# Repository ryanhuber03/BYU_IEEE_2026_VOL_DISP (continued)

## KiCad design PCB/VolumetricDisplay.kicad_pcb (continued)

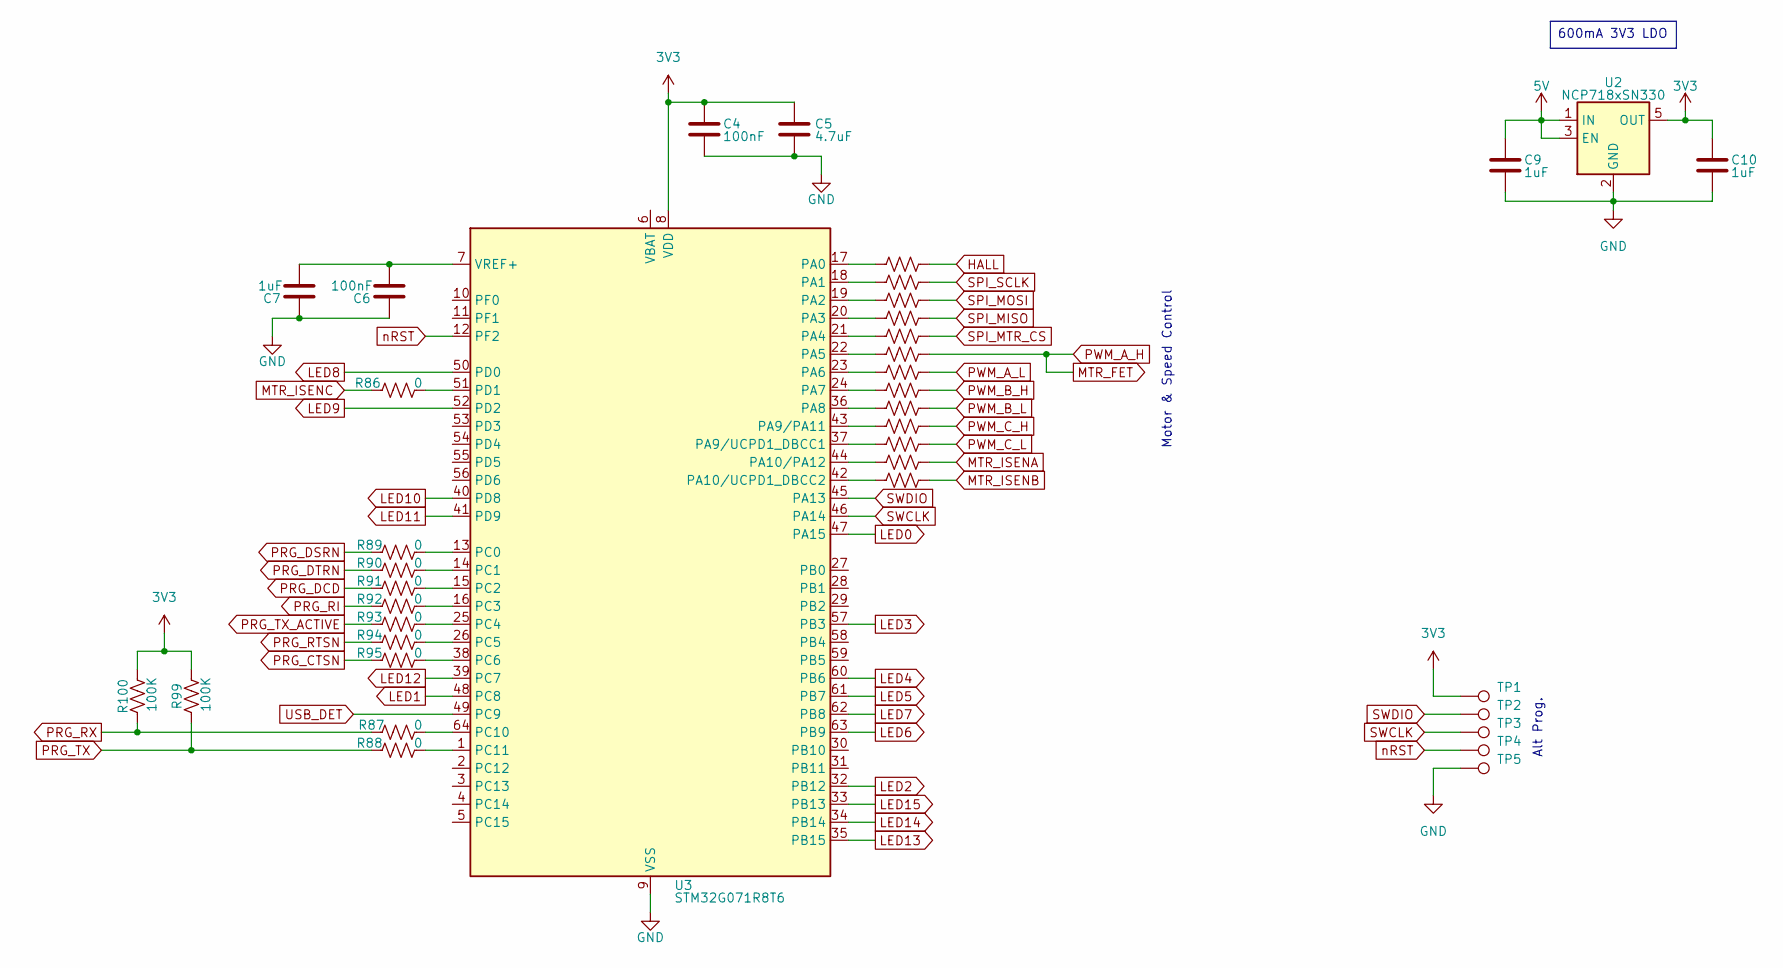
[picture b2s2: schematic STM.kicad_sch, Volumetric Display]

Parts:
C4, C6: 100nF; C_0402_1005Metric_Pad0.74x0.62mm_HandSolder
C5: 4.7uF; C_0402_1005Metric_Pad0.74x0.62mm_HandSolder
C7, C9, C10: 1uF; C_0603_1608Metric_Pad1.08x0.95mm_HandSolder
R74, R75, R76, R77, R78, R79, R80, R81, R82, R83, R84, R85, R86, R87, R88, R89, R90, R91, R92, R93, R94, R95, R96: 0; R_0603_1608Metric_Pad0.98x0.95mm_HandSolder
R99, R100: 100K; R_0603_1608Metric_Pad0.98x0.95mm_HandSolder
TP1, TP2, TP3, TP4, TP5: TestPoint; TestPoint_Pad_D1.5mm
U2: NCP718xSN330; SOT-23-5
U3: STM32G071R8T6; LQFP-64_10x10mm_P0.5mm

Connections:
3V3: C4.1, C5.1, C10.1, R99.1, R100.2, TP1.1 (1_1), U2.5 (OUT), U3.8 (VDD); also elsewhere on the board
5V: C9.1, U2.1 (IN), U2.3 (EN); also elsewhere on the board
GND: C4.2, C5.2, C6.1, C7.1, C9.2, C10.2, TP5.1 (1_1), U2.2 (GND), U3.9 (VSS); also elsewhere on the board
HALL: R96.2; also elsewhere on the board
LED0: U3.47 (PA15); also elsewhere on the board
LED1: U3.48 (PC8); also elsewhere on the board
LED2: U3.32 (PB12); also elsewhere on the board
LED3: U3.57 (PB3); also elsewhere on the board
LED4: U3.60 (PB6); also elsewhere on the board
LED5: U3.61 (PB7); also elsewhere on the board
LED6: U3.63 (PB9); also elsewhere on the board
LED7: U3.62 (PB8); also elsewhere on the board
LED8: U3.50 (PD0); also elsewhere on the board
LED9: U3.52 (PD2); also elsewhere on the board
LED10: U3.40 (PD8); also elsewhere on the board
LED11: U3.41 (PD9); also elsewhere on the board
LED12: U3.39 (PC7); also elsewhere on the board
LED13: U3.35 (PB15); also elsewhere on the board
LED14: U3.34 (PB14); also elsewhere on the board
LED15: U3.33 (PB13); also elsewhere on the board
MTR_FET: R78.2; also elsewhere on the board
MTR_ISENA: R84.2; also elsewhere on the board
MTR_ISENB: R85.2; also elsewhere on the board
MTR_ISENC: R86.2; also elsewhere on the board
unnamed: R96.1, U3.17 (PA0)
unnamed: R74.1, U3.18 (PA1)
unnamed: R75.1, U3.19 (PA2)
unnamed: R76.1, U3.20 (PA3)
unnamed: R77.1, U3.21 (PA4)
unnamed: R78.1, U3.22 (PA5)
unnamed: R79.1, U3.23 (PA6)
unnamed: R80.1, U3.24 (PA7)
unnamed: R81.1, U3.36 (PA8)
unnamed: R82.1, U3.43 (PA9/PA11)
unnamed: R83.1, U3.37 (PA9/UCPD1_DBCC1)
unnamed: R84.1, U3.44 (PA10/PA12)
unnamed: R85.1, U3.42 (PA10/UCPD1_DBCC2)
unnamed: R89.2, U3.13 (PC0)
unnamed: R90.2, U3.14 (PC1)
unnamed: R91.2, U3.15 (PC2)
unnamed: R92.2, U3.16 (PC3)
unnamed: R93.2, U3.25 (PC4)
unnamed: R94.2, U3.26 (PC5)
unnamed: R95.2, U3.38 (PC6)
unnamed: R87.2, U3.64 (PC10)
unnamed: R88.2, U3.1 (PC11)
unnamed: R86.1, U3.51 (PD1)
unnamed: C6.2, C7.2, U3.7 (VREF+)
PRG_CTSN: R95.1; also elsewhere on the board
PRG_DCD: R91.1; also elsewhere on the board
PRG_DSRN: R89.1; also elsewhere on the board
PRG_DTRN: R90.1; also elsewhere on the board
PRG_RI: R92.1; also elsewhere on the board
PRG_RTSN: R94.1; also elsewhere on the board
PRG_RX: R87.1, R100.1; also elsewhere on the board
PRG_TX: R88.1, R99.2; also elsewhere on the board
PRG_TX_ACTIVE: R93.1; also elsewhere on the board
PWM_A_L: R79.2; also elsewhere on the board
PWM_B_H: R80.2; also elsewhere on the board
PWM_B_L: R81.2; also elsewhere on the board
PWM_C_H: R82.2; also elsewhere on the board
PWM_C_L: R83.2; also elsewhere on the board
SPI_MISO: R76.2; also elsewhere on the board
SPI_MOSI: R75.2; also elsewhere on the board
SPI_MTR_CS: R77.2; also elsewhere on the board
SPI_SCLK: R74.2; also elsewhere on the board
SWCLK: TP3.1 (1_1), U3.46 (PA14)
SWDIO: TP2.1 (1_1), U3.45 (PA13)
USB_DET: U3.49 (PC9); also elsewhere on the board
nRST: TP4.1 (1_1), U3.12 (PF2)

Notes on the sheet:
Motor & Speed Control
Alt Prog.
600mA 3V3 LDO

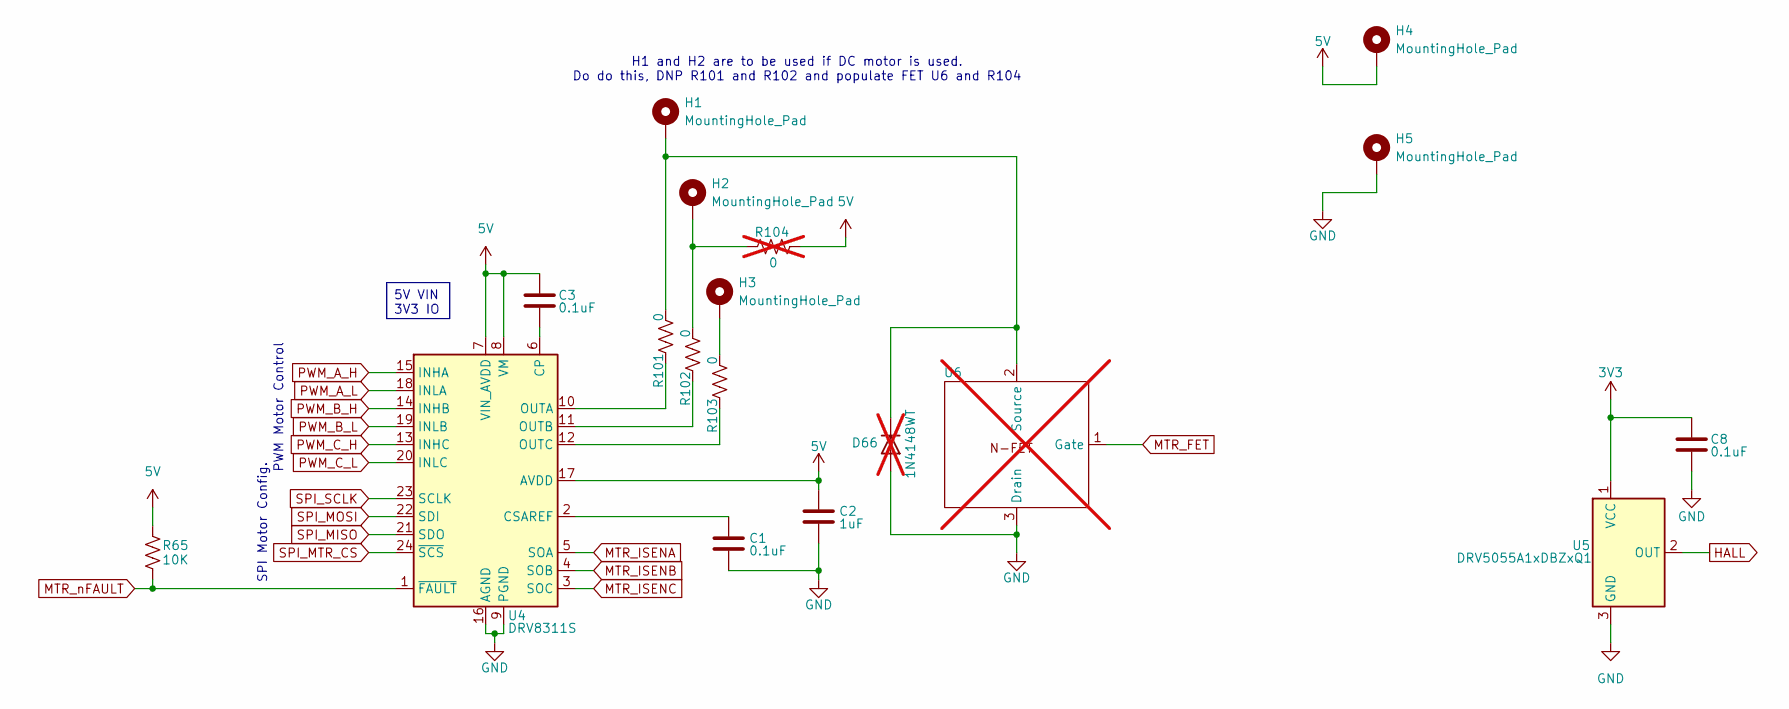
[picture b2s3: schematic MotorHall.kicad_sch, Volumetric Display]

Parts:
C1, C3: 0.1uF; C_0402_1005Metric_Pad0.74x0.62mm_HandSolder
C2: 1uF; C_0402_1005Metric_Pad0.74x0.62mm_HandSolder
C8: 0.1uF; C_0603_1608Metric_Pad1.08x0.95mm_HandSolder
D66: 1N4148WT; D_SOD-323_HandSoldering; not fitted
H1, H2, H3, H4, H5: MountingHole_Pad; 28AWG Pad
R65: 10K; R_0603_1608Metric_Pad0.98x0.95mm_HandSolder
R101, R102, R103: 0; R_0603_1608Metric_Pad0.98x0.95mm_HandSolder
R104: 0; R_0603_1608Metric_Pad0.98x0.95mm_HandSolder; not fitted
U4: DRV8311S; Texas_RRW0024A_WQFN-24-1EP_3x3mm_P0.4mm_EP1.9x1.9mm
U5: DRV5055A1xDBZxQ1; SOT-23
U6: SOT-23_Handsoldering; not fitted

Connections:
3V3: C8.2, U5.1 (VCC); also elsewhere on the board
5V: C2.1, C3.2, H4.1 (1_1), R65.1, R104.1, U4.7 (VIN_AVDD), U4.8 (VM), U4.17 (AVDD); also elsewhere on the board
GND: C1.1, C2.2, C8.1, D66.2 (A), H5.1 (1_1), U4.9 (PGND), U4.16 (AGND), U4.25 (PGND), U5.3 (GND), U6.3 (Drain); also elsewhere on the board
HALL: U5.2 (OUT); also elsewhere on the board
MTR_FET: U4.15 (INHA), U6.1 (Gate); also elsewhere on the board
MTR_ISENA: U4.5 (SOA); also elsewhere on the board
MTR_ISENB: U4.4 (SOB); also elsewhere on the board
MTR_ISENC: U4.3 (SOC); also elsewhere on the board
MTR_nFAULT: R65.2, U4.1 (~FAULT)
unnamed: D66.1 (K), H1.1 (1_1), R101.1, U6.2 (Source)
unnamed: H2.1 (1_1), R102.1, R104.2
unnamed: H3.1 (1_1), R103.1
unnamed: C3.1, U4.6 (CP)
unnamed: C1.2, U4.2 (CSAREF)
unnamed: R101.2, U4.10 (OUTA)
unnamed: R102.2, U4.11 (OUTB)
unnamed: R103.2, U4.12 (OUTC)
PWM_A_L: U4.18 (INLA); also elsewhere on the board
PWM_B_H: U4.14 (INHB); also elsewhere on the board
PWM_B_L: U4.19 (INLB); also elsewhere on the board
PWM_C_H: U4.13 (INHC); also elsewhere on the board
PWM_C_L: U4.20 (INLC); also elsewhere on the board
SPI_MISO: U4.21 (SDO); also elsewhere on the board
SPI_MOSI: U4.22 (SDI); also elsewhere on the board
SPI_MTR_CS: U4.24 (~SCS); also elsewhere on the board
SPI_SCLK: U4.23 (SCLK); also elsewhere on the board

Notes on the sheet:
PWM Motor Control
H1 and H2 are to be used if DC motor is used. Do do this, DNP R101 and R102 and populate FET U6 and R104
SPI Motor Config.
5V VIN 3V3 IO

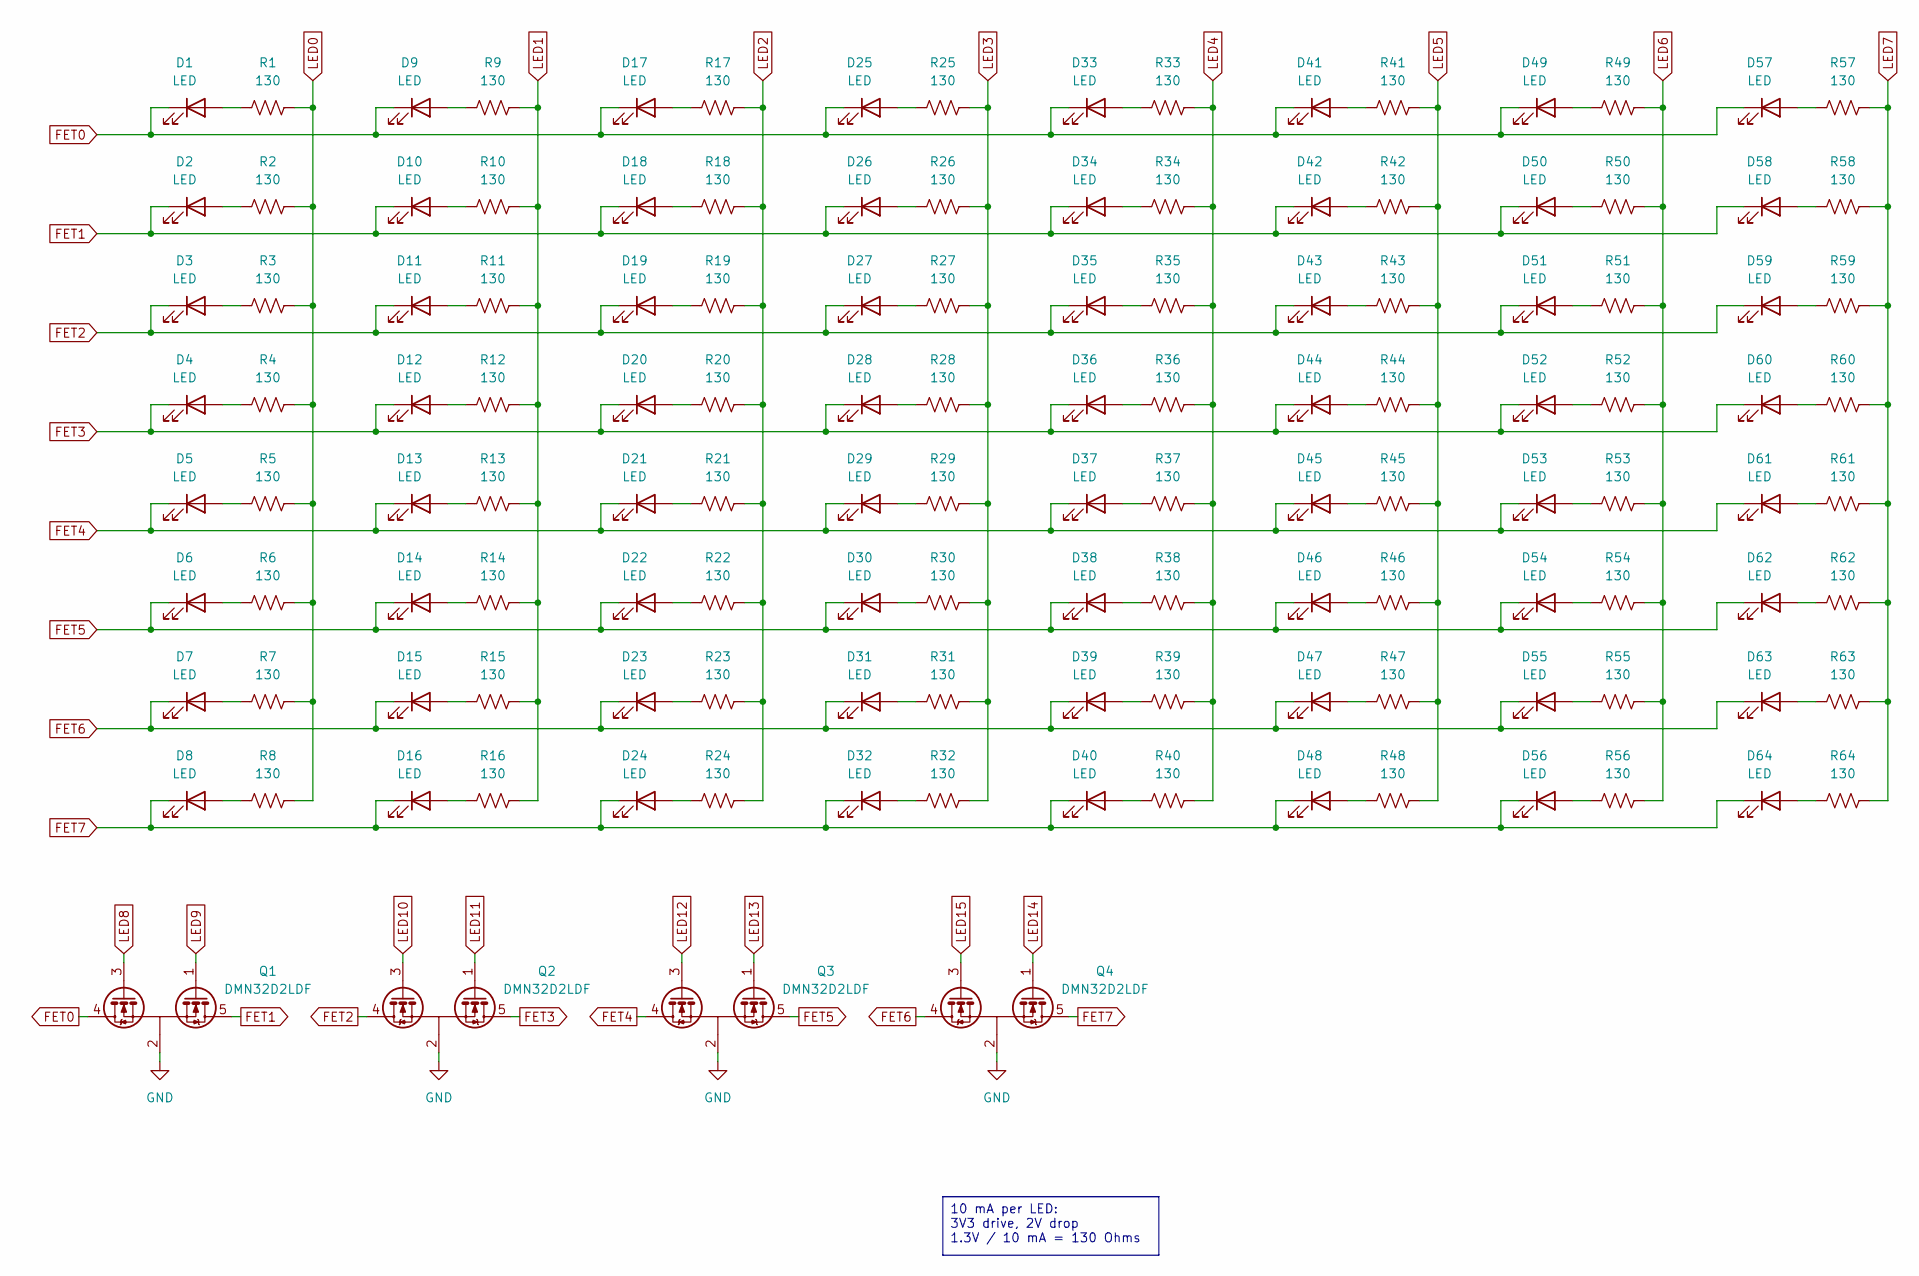
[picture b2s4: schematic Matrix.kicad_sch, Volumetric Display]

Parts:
D1, D2, D3, D4, D5, D6, D7, D8, D9, D10, D11, D12, D13, D14, D15, D16, D17, D18, D19, D20, D21, D22, D23, D24, D25, D26, D27, D28, D29, D30, D31, D32, D33, D34, D35, D36, D37, D38, D39, D40, D41, D42, D43, D44, D45, D46, D47, D48, D49, D50, D51, D52, D53, D54, D55, D56, D57, D58, D59, D60, D61, D62, D63, D64: LED; LED_0603_1608Metric_Pad1.05x0.95mm_HandSolder
Q1, Q2, Q3, Q4: DMN32D2LDF; SOT-353_SC-70-5
R1, R2, R3, R4, R5, R6, R7, R8, R9, R10, R11, R12, R13, R14, R15, R16, R17, R18, R19, R20, R21, R22, R23, R24, R25, R26, R27, R28, R29, R30, R31, R32, R33, R34, R35, R36, R37, R38, R39, R40, R41, R42, R43, R44, R45, R46, R47, R48, R49, R50, R51, R52, R53, R54, R55, R56, R57, R58, R59, R60, R61, R62, R63, R64: 130; R_0603_1608Metric_Pad0.98x0.95mm_HandSolder

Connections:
FET0: D1.1 (K), D9.1 (K), D17.1 (K), D25.1 (K), D33.1 (K), D41.1 (K), D49.1 (K), D57.1 (K), Q1.4 (D2)
FET1: D2.1 (K), D10.1 (K), D18.1 (K), D26.1 (K), D34.1 (K), D42.1 (K), D50.1 (K), D58.1 (K), Q1.5 (D1)
FET2: D3.1 (K), D11.1 (K), D19.1 (K), D27.1 (K), D35.1 (K), D43.1 (K), D51.1 (K), D59.1 (K), Q2.4 (D2)
FET3: D4.1 (K), D12.1 (K), D20.1 (K), D28.1 (K), D36.1 (K), D44.1 (K), D52.1 (K), D60.1 (K), Q2.5 (D1)
FET4: D5.1 (K), D13.1 (K), D21.1 (K), D29.1 (K), D37.1 (K), D45.1 (K), D53.1 (K), D61.1 (K), Q3.4 (D2)
FET5: D6.1 (K), D14.1 (K), D22.1 (K), D30.1 (K), D38.1 (K), D46.1 (K), D54.1 (K), D62.1 (K), Q3.5 (D1)
FET6: D7.1 (K), D15.1 (K), D23.1 (K), D31.1 (K), D39.1 (K), D47.1 (K), D55.1 (K), D63.1 (K), Q4.4 (D2)
FET7: D8.1 (K), D16.1 (K), D24.1 (K), D32.1 (K), D40.1 (K), D48.1 (K), D56.1 (K), D64.1 (K), Q4.5 (D1)
GND: Q1.2 (S), Q2.2 (S), Q3.2 (S), Q4.2 (S); also elsewhere on the board
LED0: R1.2, R2.2, R3.2, R4.2, R5.2, R6.2, R7.2, R8.2; also elsewhere on the board
LED1: R9.2, R10.2, R11.2, R12.2, R13.2, R14.2, R15.2, R16.2; also elsewhere on the board
LED2: R17.2, R18.2, R19.2, R20.2, R21.2, R22.2, R23.2, R24.2; also elsewhere on the board
LED3: R25.2, R26.2, R27.2, R28.2, R29.2, R30.2, R31.2, R32.2; also elsewhere on the board
LED4: R33.2, R34.2, R35.2, R36.2, R37.2, R38.2, R39.2, R40.2; also elsewhere on the board
LED5: R41.2, R42.2, R43.2, R44.2, R45.2, R46.2, R47.2, R48.2; also elsewhere on the board
LED6: R49.2, R50.2, R51.2, R52.2, R53.2, R54.2, R55.2, R56.2; also elsewhere on the board
LED7: R57.2, R58.2, R59.2, R60.2, R61.2, R62.2, R63.2, R64.2; also elsewhere on the board
LED8: Q1.3 (G2); also elsewhere on the board
LED9: Q1.1 (G1); also elsewhere on the board
LED10: Q2.3 (G2); also elsewhere on the board
LED11: Q2.1 (G1); also elsewhere on the board
LED12: Q3.3 (G2); also elsewhere on the board
LED13: Q3.1 (G1); also elsewhere on the board
LED14: Q4.1 (G1); also elsewhere on the board
LED15: Q4.3 (G2); also elsewhere on the board
unnamed: D1.2 (A), R1.1
unnamed: D2.2 (A), R2.1
unnamed: D3.2 (A), R3.1
unnamed: D4.2 (A), R4.1
unnamed: D5.2 (A), R5.1
unnamed: D6.2 (A), R6.1
unnamed: D7.2 (A), R7.1
unnamed: D8.2 (A), R8.1
unnamed: D9.2 (A), R9.1
unnamed: D10.2 (A), R10.1
unnamed: D11.2 (A), R11.1
unnamed: D12.2 (A), R12.1
unnamed: D13.2 (A), R13.1
unnamed: D14.2 (A), R14.1
unnamed: D15.2 (A), R15.1
unnamed: D16.2 (A), R16.1
unnamed: D17.2 (A), R17.1
unnamed: D18.2 (A), R18.1
unnamed: D19.2 (A), R19.1
unnamed: D20.2 (A), R20.1
unnamed: D21.2 (A), R21.1
unnamed: D22.2 (A), R22.1
unnamed: D23.2 (A), R23.1
unnamed: D24.2 (A), R24.1
unnamed: D25.2 (A), R25.1
unnamed: D26.2 (A), R26.1
unnamed: D27.2 (A), R27.1
unnamed: D28.2 (A), R28.1
unnamed: D29.2 (A), R29.1
unnamed: D30.2 (A), R30.1
unnamed: D31.2 (A), R31.1
unnamed: D32.2 (A), R32.1
unnamed: D33.2 (A), R33.1
unnamed: D34.2 (A), R34.1
unnamed: D35.2 (A), R35.1
unnamed: D36.2 (A), R36.1
unnamed: D37.2 (A), R37.1
unnamed: D38.2 (A), R38.1
unnamed: D39.2 (A), R39.1
unnamed: D40.2 (A), R40.1
unnamed: D41.2 (A), R41.1
unnamed: D42.2 (A), R42.1
unnamed: D43.2 (A), R43.1
unnamed: D44.2 (A), R44.1
unnamed: D45.2 (A), R45.1
unnamed: D46.2 (A), R46.1
unnamed: D47.2 (A), R47.1
unnamed: D48.2 (A), R48.1
unnamed: D49.2 (A), R49.1
unnamed: D50.2 (A), R50.1
unnamed: D51.2 (A), R51.1
unnamed: D52.2 (A), R52.1
unnamed: D53.2 (A), R53.1
unnamed: D54.2 (A), R54.1
unnamed: D55.2 (A), R55.1
unnamed: D56.2 (A), R56.1
unnamed: D57.2 (A), R57.1
unnamed: D58.2 (A), R58.1
unnamed: D59.2 (A), R59.1
unnamed: D60.2 (A), R60.1
unnamed: D61.2 (A), R61.1
unnamed: D62.2 (A), R62.1
unnamed: D63.2 (A), R63.1
unnamed: D64.2 (A), R64.1

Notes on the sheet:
10 mA per LED: 3V3 drive, 2V drop 1.3V / 10 mA = 130 Ohms

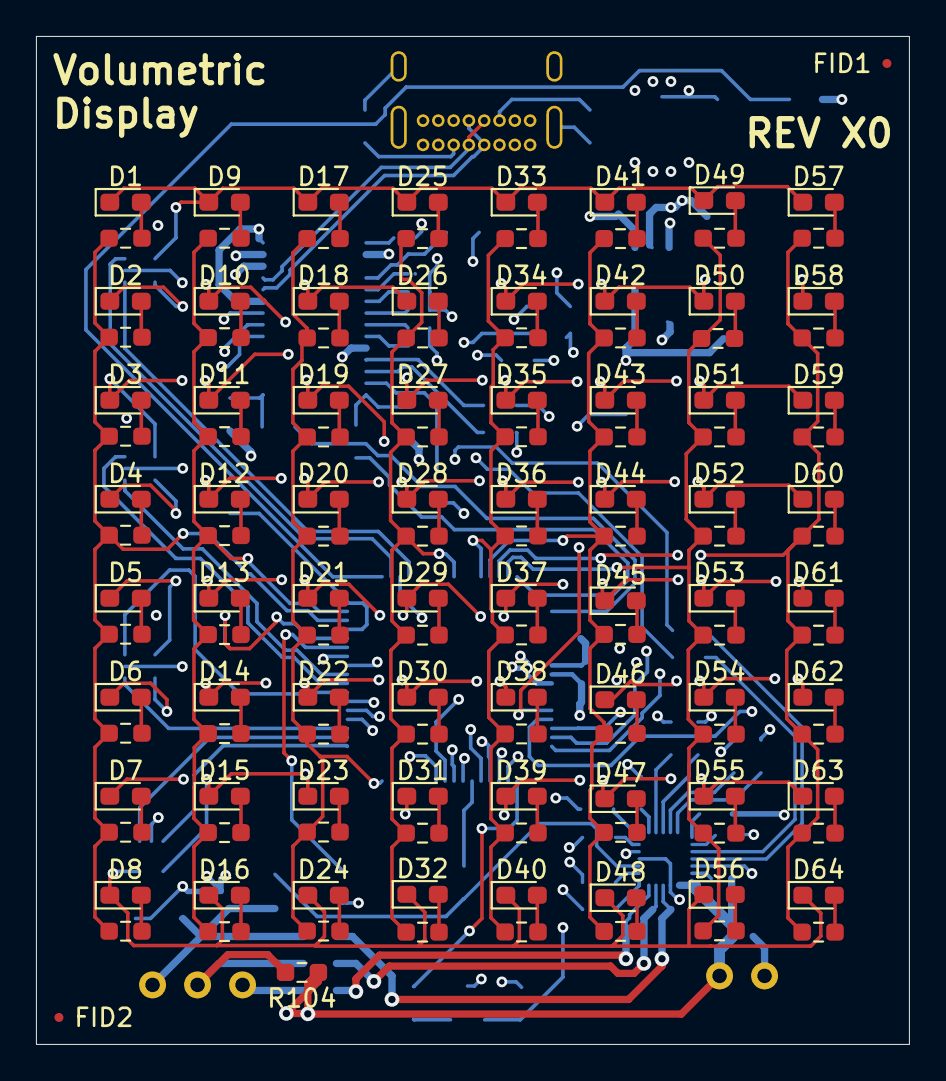
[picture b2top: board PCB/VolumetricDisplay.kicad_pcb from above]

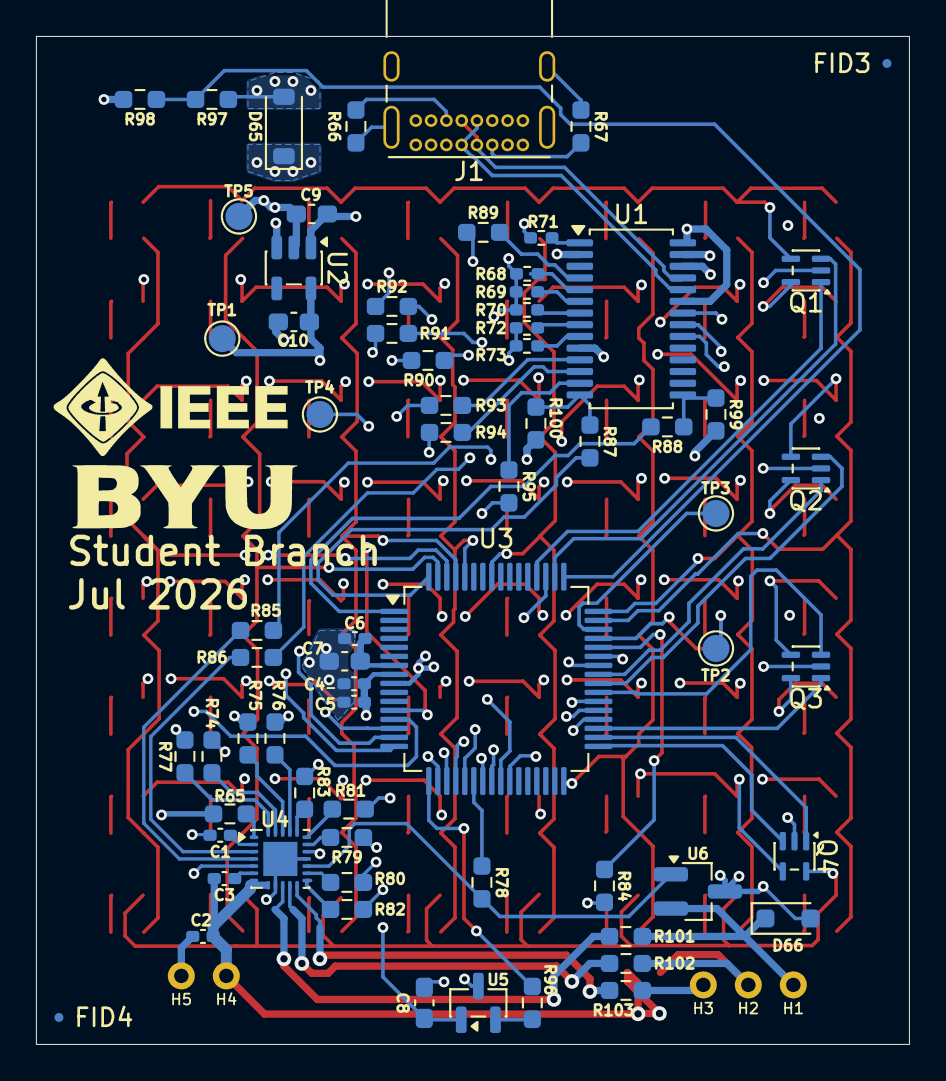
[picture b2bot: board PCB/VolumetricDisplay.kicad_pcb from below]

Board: 4 copper layers, 48.5 x 56.0 mm, 205 parts (74 on the bottom side), 163 nets.

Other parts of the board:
FID1, FID2, FID3, FID4: Fiducial; Fiducial_0.5mm_Mask1mm

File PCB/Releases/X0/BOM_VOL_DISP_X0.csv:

Designator,Qty,Comment,DNP,Exclude from BOM,Exclude from Board,Footprint,Datasheet,JLCPCB Part #
"C1,C3",2,0.1uF,,,,Capacitor_SMD:C_0402_1005Metric_Pad0.74x0.62mm_HandSolder,,C1525
C2,1,1uF,,,,Capacitor_SMD:C_0402_1005Metric_Pad0.74x0.62mm_HandSolder,,C52923
"C4,C6",2,100nF,,,,Capacitor_SMD:C_0402_1005Metric_Pad0.74x0.62mm_HandSolder,,C1525
C5,1,4.7uF,,,,Capacitor_SMD:C_0402_1005Metric_Pad0.74x0.62mm_HandSolder,,C23733
"C7,C9,C10",3,1uF,,,,Capacitor_SMD:C_0603_1608Metric_Pad1.08x0.95mm_HandSolder,,C15849
C8,1,0.1uF,,,,Capacitor_SMD:C_0603_1608Metric_Pad1.08x0.95mm_HandSolder,,C14663
"D1,D2,D3,D4,D5,D6,D7,D8,D9,D10,D11,D12,D13,D14,D15,D16,D17,D18,D19,D20,D21,D22,D23,D24,D25,D26,D27,D28,D29,D30,D31,D32,D33,D34,D35,D36,D37,D38,D39,D40,D41,D42,D43,D44,D45,D46,D47,D48,D49,D50,D51,D52,D53,D54,D55,D56,D57,D58,D59,D60,D61,D62,D63,D64",64,LED,,,,LED_SMD:LED_0603_1608Metric_Pad1.05x0.95mm_HandSolder,,C2286
D65,1,MBR0560,,,,Diode_SMD:D_SOD-123,http://www.mccsemi.com/up_pdf/MBR0520~MBR0580(SOD123).pdf,C150515
D66,1,1N4148WT,DNP,,,Diode_SMD:D_SOD-323_HandSoldering,https://www.diodes.com/assets/Datasheets/ds30396.pdf,
J1,1,USB_C_Receptacle_USB2.0_16P,,,,Connector_USB:USB_C_Receptacle_GCT_USB4085,https://www.usb.org/sites/default/files/documents/usb_type-c.zip,C7095263
"Q1,Q2,Q3,Q4",4,MMFTN620KD,,,,Package_TO_SOT_SMD:SOT-457T,,C5769818
"R1,R2,R3,R4,R5,R6,R7,R8,R9,R10,R11,R12,R13,R14,R15,R16,R17,R18,R19,R20,R21,R22,R23,R24,R25,R26,R27,R28,R29,R30,R31,R32,R33,R34,R35,R36,R37,R38,R39,R40,R41,R42,R43,R44,R45,R46,R47,R48,R49,R50,R51,R52,R53,R54,R55,R56,R57,R58,R59,R60,R61,R62,R63,R64",64,130,,,,Resistor_SMD:R_0603_1608Metric_Pad0.98x0.95mm_HandSolder,,C22797
R65,1,10K,,,,Resistor_SMD:R_0603_1608Metric_Pad0.98x0.95mm_HandSolder,,C25804
"R66,R67",2,5.1K,,,,Resistor_SMD:R_0603_1608Metric_Pad0.98x0.95mm_HandSolder,,C23186
"R68,R69,R70,R71,R72,R73",6,0,,,,Resistor_SMD:R_0402_1005Metric_Pad0.72x0.64mm_HandSolder,,C17168
"R74,R75,R76,R77,R78,R79,R80,R81,R82,R83,R84,R85,R86,R87,R88,R89,R90,R91,R92,R93,R94,R95,R96,R101,R102,R103",26,0,,,,Resistor_SMD:R_0603_1608Metric_Pad0.98x0.95mm_HandSolder,,C21189
"R97,R98",2,50K,,,,Resistor_SMD:R_0603_1608Metric_Pad0.98x0.95mm_HandSolder,,C23184
"R99,R100",2,100K,,,,Resistor_SMD:R_0603_1608Metric_Pad0.98x0.95mm_HandSolder,,C25803
R104,1,0,DNP,,,Resistor_SMD:R_0603_1608Metric_Pad0.98x0.95mm_HandSolder,,
U1,1,FT260S-R,,,,Package_SO:TSSOP-28_4.4x9.7mm_P0.65mm,,C3313267
U2,1,NCP718xSN330,,,,Package_TO_SOT_SMD:SOT-23-5,https://www.onsemi.com/pub/Collateral/NCP718-D.PDF,C892795
U3,1,STM32G071R8T6,,,,Package_QFP:LQFP-64_10x10mm_P0.5mm,https://www.st.com/resource/en/datasheet/stm32g071rb.pdf,C432214
U4,1,DRV8311S,,,,Package_DFN_QFN:Texas_RRW0024A_WQFN-24-1EP_3x3mm_P0.4mm_EP1.9x1.9mm,https://www.ti.com/lit/ds/symlink/drv8311.pdf,C9900084880
U5,1,DRV5055A1xDBZxQ1,,,,Package_TO_SOT_SMD:SOT-23,https://www.ti.com/lit/ds/symlink/drv5055-q1.pdf,C962987
U6,1,,DNP,,,Package_TO_SOT_SMD:SOT-23_Handsoldering,,

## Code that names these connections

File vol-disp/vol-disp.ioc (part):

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Mcu.Name=STM32G071R(6-8-B)Tx
Mcu.Package=LQFP64
Mcu.UserName=STM32G071R8Tx
PA0.Signal=GPIO_Analog
PA1.Signal=SPI1_SCK
PA10.Signal=GPIO_Analog
PA11\ [PA9].Signal=GPIO_Output
PA12\ [PA10].Signal=GPIO_Analog
PA13.Mode=Serial_Wire
PA13.Signal=SYS_SWDIO
PA14-BOOT0.Mode=Serial_Wire
PA14-BOOT0.Signal=SYS_SWCLK
PA15.Signal=GPIO_Output
PA2.Signal=SPI1_MOSI
PA3.Signal=SPI2_MISO
PA4.Signal=SPI1_NSS
PA5.Signal=GPIO_Output
PA6.Signal=GPIO_Output
PA7.Signal=GPIO_Output
PA8.Signal=GPIO_Output
PA9.Signal=GPIO_Output
PB12.Signal=GPIO_Output
PB13.Signal=GPIO_Output
PB14.Signal=GPIO_Output
PB15.Signal=GPIO_Output
PB3.Signal=GPIO_Output
PB6.Signal=GPIO_Output
PB7.Signal=GPIO_Output
PB8.Signal=GPIO_Output
PB9.Signal=GPIO_Output
PC0.Signal=GPIO_Output
PC1.Signal=GPIO_Output
PC10.Signal=USART3_TX
PC11.Signal=USART3_RX
PC2.Signal=GPXTI2
PC3.Signal=GPIO_Output
PC4.Signal=GPIO_Output
PC5.Signal=GPIO_Output
PC6.Signal=GPIO_Output
PC7.Signal=GPIO_Output
PC8.Signal=GPIO_Output
PC9.Signal=GPIO_Input
PD0.Signal=GPIO_Output
PD1.Signal=GPIO_Analog
PD2.Signal=GPIO_Output
PD8.Signal=GPIO_Output
PD9.Signal=GPIO_Output
RCC.HSE_VALUE=8000000
RCC.SYSCLKFreq_VALUE=64000000
RCC.SYSCLKSource=RCC_SYSCLKSOURCE_PLLCLK
board=custom
